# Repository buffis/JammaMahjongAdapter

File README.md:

# JammaMahjongAdapter
 
Allows playing Mahjong PCBs on jamma wired cabinets.

Note: Adapter above are missing some final touches present on cad files.

Features:
- Connectors for Mahjong COM and KEY pins
- KEY pins wired to P1 controls (see silkscreen)
- COM pins wired to P2 controls (see silkscreen)
- Switch for Mahjong AUDIO-. Either connects it to SPK- or GND, see note below.
- Optional jumper on the bottom for connecting -5V

Fabrication notes:
- This is a four layer PCB
- You might want gold finger finishing

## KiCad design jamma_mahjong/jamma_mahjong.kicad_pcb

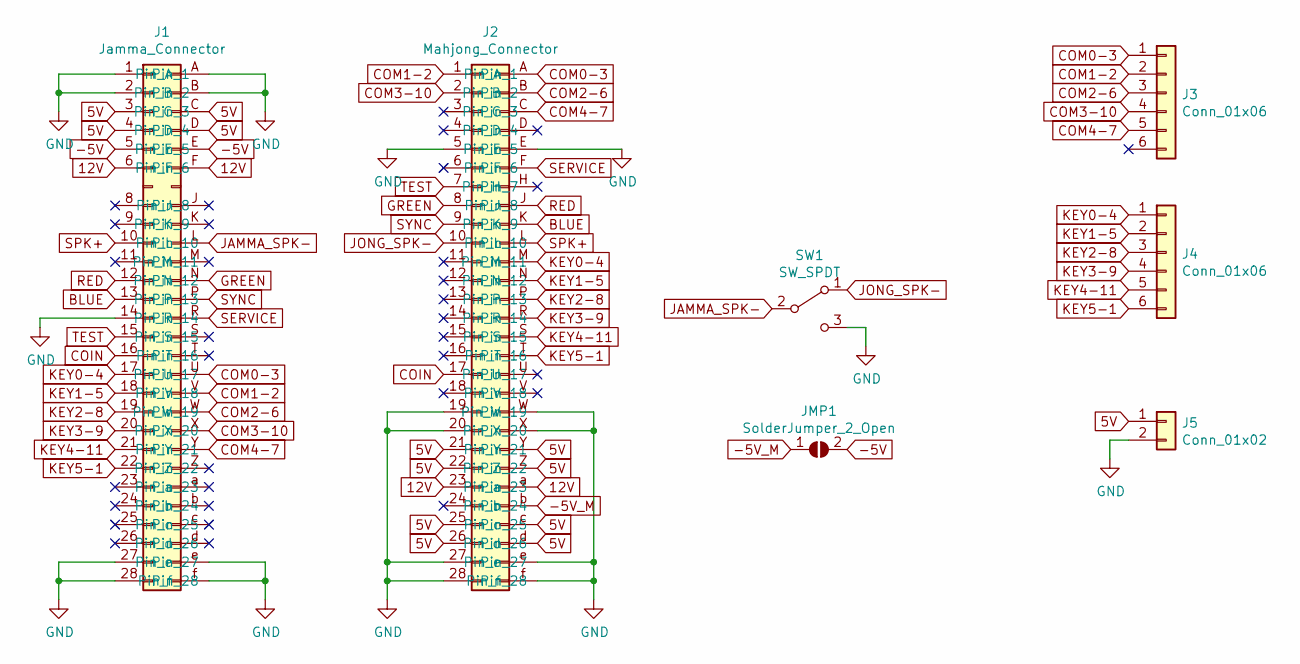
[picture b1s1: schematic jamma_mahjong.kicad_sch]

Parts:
J1: Jamma_Connector; JAMMA-56
J2: Mahjong_Connector; MAHJONG-56
J3, J4: Conn_01x06; JST_EH_B6B-EH-A_1x06_P2.50mm_Vertical
J5: Conn_01x02; JST_EH_B2B-EH-A_1x02_P2.50mm_Vertical
JMP1: SolderJumper_2_Open; R_0805_2012Metric_Pad1.20x1.40mm_HandSolder
SW1: SW_SPDT; A101SYCQ04

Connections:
5V: J1.3, J1.4, J1.C, J1.D, J2.21, J2.22, J2.25, J2.26, J2.Y, J2.Z, J2.c, J2.d, J5.1
12V: J1.6, J1.F, J2.23, J2.a
-5V: J1.5, J1.E, JMP1.2 (B)
-5V_M: J2.b, JMP1.1 (A)
BLUE: J1.13, J2.K
COIN: J1.16, J2.17
COM0-3: J1.U, J2.A, J3.1
COM1-2: J1.V, J2.1, J3.2
COM2-6: J1.W, J2.B, J3.3
COM3-10: J1.X, J2.2, J3.4
COM4-7: J1.Y, J2.C, J3.5
GND: J1.1, J1.2, J1.14, J1.27, J1.28, J1.A, J1.B, J1.e, J1.f, J2.5, J2.19, J2.20, J2.27, J2.28, J2.E, J2.W, J2.X, J2.e, J2.f, J5.2, SW1.3 (C)
GREEN: J1.N, J2.8
JAMMA_SPK-: J1.L, SW1.2 (B)
JONG_SPK-: J2.10, SW1.1 (A)
KEY0-4: J1.17, J2.M, J4.1
KEY1-5: J1.18, J2.N, J4.2
KEY2-8: J1.19, J2.P, J4.3
KEY3-9: J1.20, J2.R, J4.4
KEY4-11: J1.21, J2.S, J4.5
KEY5-1: J1.22, J2.T, J4.6
RED: J1.12, J2.J
SERVICE: J1.R, J2.F
SPK+: J1.10, J2.L
SYNC: J1.P, J2.9
TEST: J1.15, J2.7

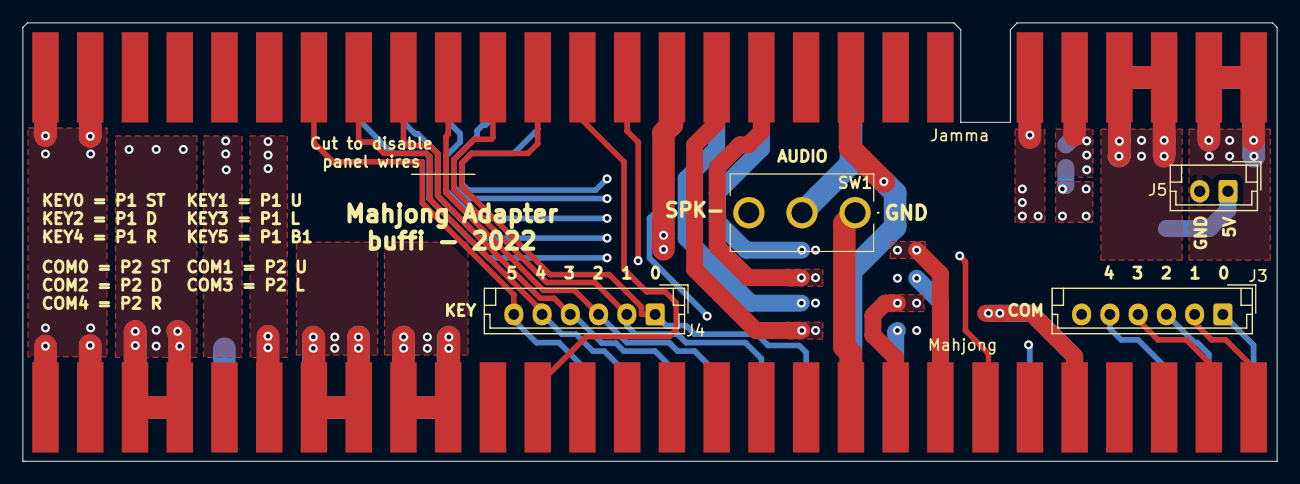
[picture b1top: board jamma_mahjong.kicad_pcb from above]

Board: 4 copper layers, 111.0 x 38.8 mm, 7 parts (1 on the bottom side), 26 nets.

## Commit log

2021-12-28 stuff
2022-01-22 More stuff
2022-01-22 Remove soldermask from pin, add clearance under cuttable parts. Add image
2022-01-22 minor fixes, new gerbers
2022-01-23 fix soldermask
2022-02-01 Fix silkscreen for SPK switcher (oops)
2022-02-02 Minor fixes
